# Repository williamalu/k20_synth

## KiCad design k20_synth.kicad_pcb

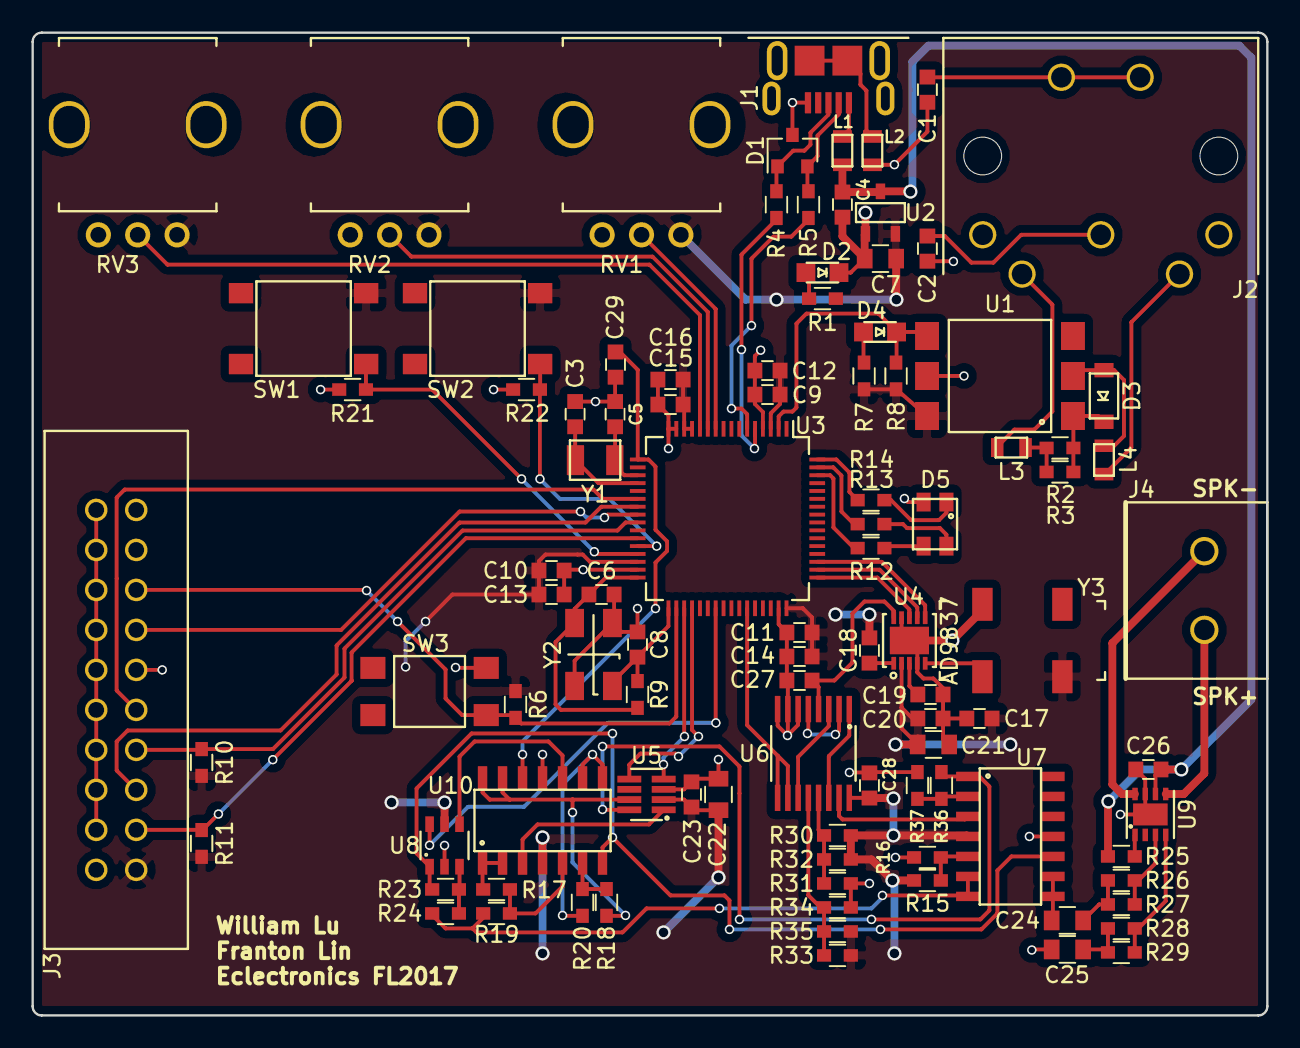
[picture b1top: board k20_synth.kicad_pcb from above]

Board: 2 copper layers, 78.4 x 62.4 mm, 98 parts (0 on the bottom side), 79 nets.

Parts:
C1, C2, C9, C10, C11, C15, C16, C17, C19, C20, C23, C28, C29: 0.1uF; C_0603
C3, C5, C6, C8: 22pF; C_0603
C4, C12, C13, C14, C26: 1uF; C_0603
C7, C21, C22: 10uF; C_0805
C18: 10nF; C_0603
C24, C25: 33uF; C_0805
C27: 1nF; C_0603
D1: D_TVS_x2_AAC; SOT-23
D2, D4: LED; LTST-C170TGKT
D3: D; 1N4148W-TP
D5: LED_CRGB_altpin; XZM2CRKM2DGFBB45SCCB
J1: USB_OTG_PWR; 2040002-1
J2: MIDI-DIN-5; SDF-50J
J3: Conn_02x10_Odd_Even; SBH11-PBPC-D10-ST-BK
J4: Spk_Screw_Terminal_01x02; OSTTA020161
L1, L2: 330; MPZ2012S331AT000
L3, L4: 1k@100MHz; MMZ2012R102AT000
R1, R7, R37: 1k; R_0603
R2: 806; R_0603
R3: 301; R_0603
R4, R5: 33; R_0603
R6, R15, R16, R17, R18, R19, R20, R21, R22, R25: 10k; R_0603
R8: 200; R_0603
R9: 1M; R_0603
R10, R11: 100k; R_0603
R12, R13: 30.1; R_0603
R14: 127; R_0603
R23: 6.98k; R_0603
R24: 1.58k; R_0603
R26, R27, R28, R29: 909; R_0603
R30: 499k; R_0603
R31: 3.01k; R_0603
R32, R35: 12.7k; R_0603
R33: 2M; R_0603
R34: 143; R_0603
R36: 4.02k; R_0603
RV1, RV2, RV3: POT; PTV09A-4020U
SW1, SW2: SW_Push_Dual_x2; PTS645SM43SMTR92
SW3: SW_Push_Dual_x2; TL3305AF160QG
U1: H11L1; H11L1S(TA)
U2: MCP1702T-3302E/CB; MCP1702T-3302E
U3: MK20DX128VLH5; LQFP-64_10x10mm_Pitch0.5mm
U4: AD9837; AD9837BCPZ-RL
U5: AD5245BRJZ10-RL7
U6: CD74HC4053PWR
U7, U10: MCP6024; MCP6024T-I(SL)
U8: SN74LVC1G3157; SN74LVC1G3157DBVR
U9: TS4962IQT; TS4962IQT(DFN)
Y1: Crystal; ECS-.327-12.5-34B-TR
Y2: Crystal_GND24; ABM3B-8.000MHZ-B2-T
Y3: SG-636PCE5.0000MC0

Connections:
+3V3: C7.2, C9.1, C10.1, C11.1, C12.1, C13.1, C14.1, C15.1, C16.1, C17.1, C18.2, C20.1, C21.1, C22.2, C23.2, C28.1, J3.1, R1.2, R6.1, R7.1, R8.1, R10.1, R11.1, R15.2, R30.1, R32.1, R33.2, R35.2, RV1.3, RV2.3, RV3.3, SW1.3, SW2.3, U1.6, U2.2, U3.3, U3.13, U3.14, U3.30, U3.48, U4.2, U5.2, U6.16, U7.4, U8.5, U10.4, Y3.4
+5V: C4.2, C26.2, L2.1, R25.1, U2.3, U9.6
/ADC0_DM0: RV1.2, U3.10
/ADC0_DM3: RV3.2, U3.12
/ADC0_DP3: RV2.2, U3.11
/FTM1_CH0: R22.2, SW2.1, U3.28
/FTM1_CH1: R21.2, SW1.1, U3.29
/I2C0_SCL: U3.35, U5.4
/I2C0_SDA: U3.36, U5.5
/JTAG_TCLK: J3.9, U3.22
/JTAG_TDI: J3.5, U3.23
/JTAG_TDO: J3.13, U3.24
/JTAG_TMS: J3.7, R10.2, U3.25
/LED_BLUE: R12.1, U3.62
/LED_GREEN: R13.1, U3.63
/LED_RED: R14.1, U3.64
/MIDI_IN: D4.1, R8.2, U1.4, U3.2
/NORM_WAVEGEN: R36.2, U5.8, U7.1
/PTB16: U3.39, U8.6
/SPI0_PCS0: U3.49, U4.8
/SPI0_SCK: U3.50, U4.7
/SPI0_SOUT: U3.51, U4.6
/USB_DM: R5.1, U3.6
/USB_DP: R4.1, U3.5
/VREF_OUT: C29.1, U3.17, U10.12
/WAVEGEN: C27.1, U4.10, U6.4
/~JTAG_TRST: J3.3, R11.2, U3.27
/~RESET: J3.15, R6.2, SW3.2, U3.34
/~SQUARE: U3.43, U6.9, U6.10
GND: C1.2, C2.2, C3.2, C4.1, C5.2, C6.2, C7.1, C8.2, C9.2, C10.2, C11.2, C12.2, C13.2, C14.2, C15.2, C16.2, C17.2, C19.1, C20.2, C21.2, C22.1, C23.1, C25.2, C26.1, C27.2, C28.2, C29.2, D1.3, D2.1, D5.4, J1.5, J3.4, J3.6, J3.8, J3.10, J3.11, J3.12, J3.14, J3.16, J3.18, J3.20, L1.2, R16.1, R21.1, R22.1, R31.2, R34.2, R37.1, RV1.1, RV2.1, RV3.1, SW3.4, U1.5, U2.1, U3.4, U3.15, U3.16, U3.31, U3.47, U4.4, U4.9, U4.11, U5.3, U6.6, U6.7, U6.8, U7.11, U8.2, U9.7, U9.9, U10.11, Y2.2, Y2.4, Y3.2
unnamed: C1.1, J2.~
unnamed: C2.1, J2.2
unnamed: C3.1, U3.20, Y1.1
unnamed: C5.1, U3.19, Y1.2
unnamed: C6.1, R9.2, U3.32, Y2.3
unnamed: C8.1, R9.1, U3.33, Y2.1
unnamed: C18.1, U4.1
unnamed: C19.2, U4.3
unnamed: C24.1, R26.1, R27.1
unnamed: C24.2, U7.8, U7.9
unnamed: C25.1, R28.1, R29.1
unnamed: D1.1, J1.3, R4.2
unnamed: D1.2, J1.2, R5.2
unnamed: D2.2, R1.1
unnamed: D3.1, R2.1, R3.1, U1.1
unnamed: D3.2, L4.1, U1.2
unnamed: D4.2, R7.2
unnamed: D5.1, R14.2
unnamed: D5.2, R13.2
unnamed: D5.3, R12.2
unnamed: J1.1, L2.2
unnamed: J1.6, L1.1
unnamed: J2.4, L3.2
unnamed: J2.5, L4.2
unnamed: J4.1, U9.8
unnamed: J4.2, U9.5
unnamed: L3.1, R2.2, R3.2
unnamed: R15.1, R16.2, U7.5
unnamed: R17.1, R19.2, U10.5
unnamed: R17.2, U10.1, U10.2
unnamed: R18.1, R20.2, U10.6
unnamed: R18.2, U5.7, U10.13, U10.14
unnamed: R19.1, R24.1, U7.6, U7.7
unnamed: R20.1, U10.8, U10.9
unnamed: R23.1, R24.2, U8.3
unnamed: R23.2, U7.10, U8.1, U10.7
unnamed: R25.2, U9.1
unnamed: R26.2, R27.2, U9.3
unnamed: R28.2, R29.2, U9.4
unnamed: R30.2, R31.1, R32.2, U6.13
unnamed: R33.1, R34.1, R35.1, U6.12
unnamed: R36.1, R37.2, U7.2
unnamed: U4.5, Y3.3
unnamed: U6.1, U6.14
unnamed: U6.2, U6.5
unnamed: U6.3, U6.11
unnamed: U6.15, U7.3
unnamed: U5.1, U10.3
unnamed: U8.4, U10.10

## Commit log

2017-10-30 added kicad gitignore
2017-11-02 converted k20_dev_board project and added beginnings of DDS circuit
2017-11-02 Added DDS oscillator, audio amplifier, wavegen output buffer
2017-11-02 Replaced pot and switch with digipot and mux
2017-11-06 cleaned up gpio, added control pots/buttons
2017-11-06 changed op-amp part to mcp6024/6022
2017-11-13 cleaned up schematic
2017-11-16 Added square wave normalizing circuit
2017-11-16 Created and associated some footprints
2017-11-16 Created and associated more footprints, fixed buttons
2017-11-17 Finished footprints
2017-11-17 Specced audio amplifier blocking caps
2017-11-17 .gitignore
2017-11-17 Fixed electrical rules checker problems
2017-11-18 doublechecked footprints
2017-11-18 Attempted some layout or something
2017-11-18 Deleted some random no connects
2017-11-18 so many crashes
2017-11-18 Finished layout, hopefully it works
2017-11-18 Added our names for posterity
2017-11-27 Added BOM
2017-11-30 Fixed footprint masks, potentiometer footprints and spacing
2017-11-30 fixed weird gitignore problems
2017-12-01 updated pot footprint
